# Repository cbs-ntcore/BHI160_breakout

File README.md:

# BHI160_breakout
Simple breakout board for the BHI160 IMU

WARNING this has not yet been ordered.

The project is available on oshpark https://oshpark.com/shared_projects/33BVj4D2

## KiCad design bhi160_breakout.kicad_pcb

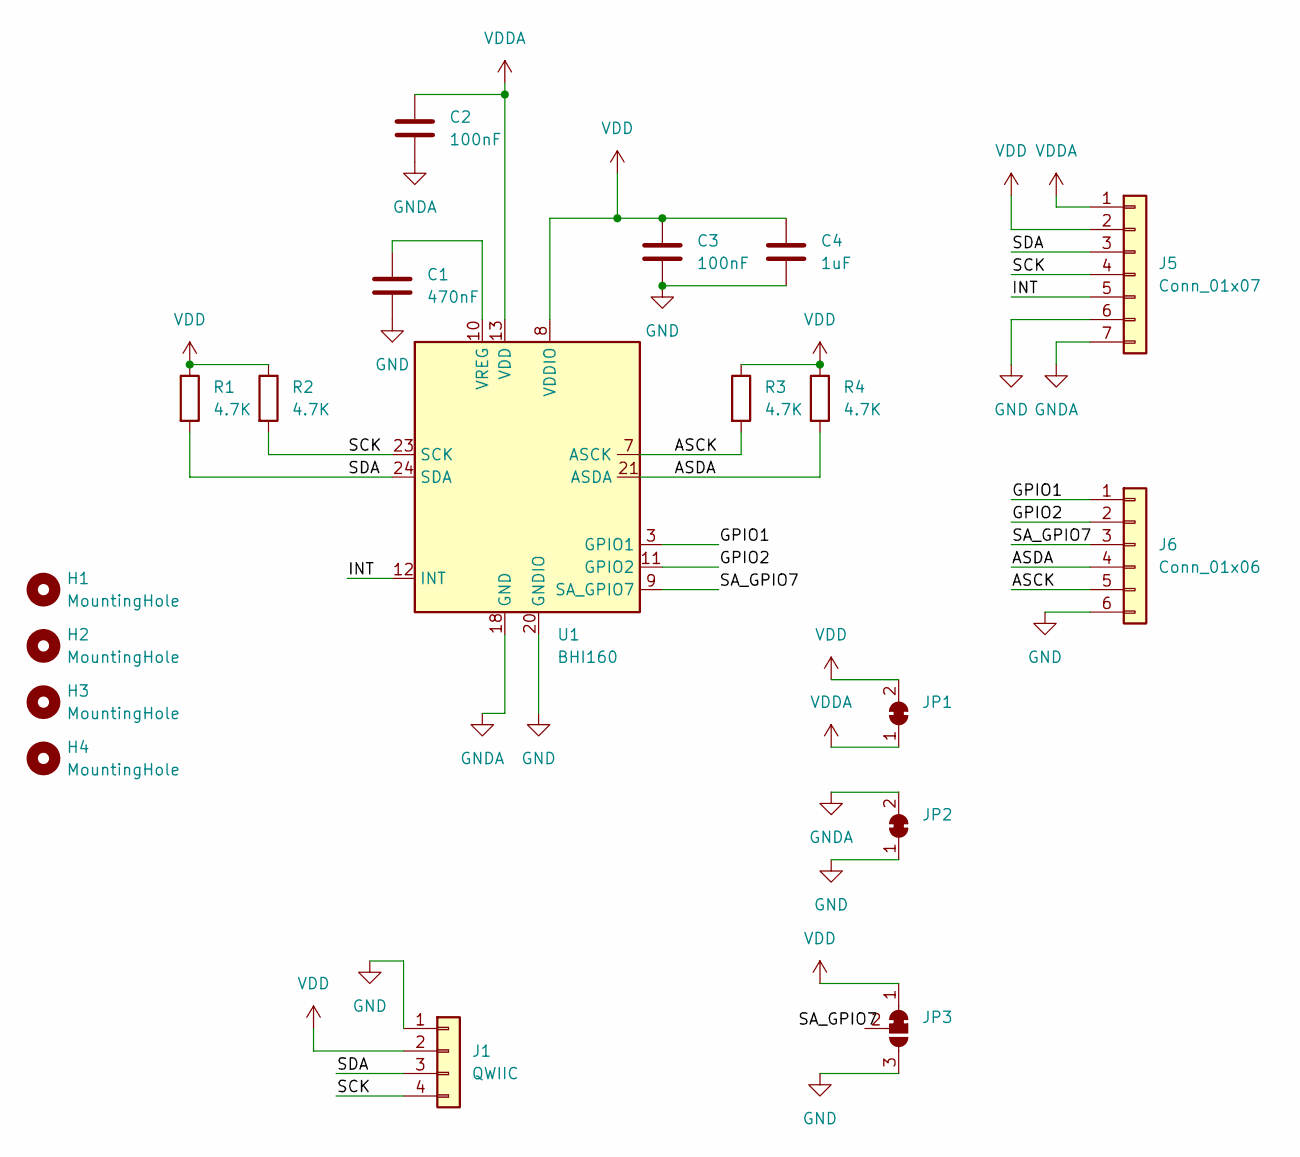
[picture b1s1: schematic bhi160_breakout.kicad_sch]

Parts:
C1: 470nF
C2, C3: 100nF
C4: 1uF
H1, H2, H3, H4: MountingHole; MountingHole_3.2mm_M3
J1: QWIIC; JST_SH_BM04B-SRSS-TB_1x04-1MP_P1.00mm_Vertical
J5: Conn_01x07; PinHeader_1x07_P2.54mm_Vertical
J6: Conn_01x06; PinHeader_1x06_P2.54mm_Vertical
JP1, JP2, JP3: (no value)
R1, R2, R3, R4: 4.7K
U1: BHI160; LGA-24_3x3mm_P0.4mm

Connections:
/ASCK: J6.5, R3.2, U1.7 (ASCK)
/ASDA: J6.4, R4.2, U1.21 (ASDA)
/GPIO1: J6.1, U1.3 (GPIO1)
/GPIO2: J6.2, U1.11 (GPIO2)
/INT: J5.5, U1.12 (INT)
/SA_GPIO7: J6.3, U1.9 (SA_GPIO7)
/SCK: J1.4, J5.4, R2.2, U1.23 (SCK)
/SDA: J1.3, J5.3, R1.2, U1.24 (SDA)
GND: C1.2, C3.2, C4.2, J1.1, J5.6, J6.6, JP2.1 (A), JP3.3 (B), U1.20 (GNDIO)
GNDA: C2.2, J5.7, JP2.2 (B), U1.18 (GND)
unnamed: C1.1, U1.10 (VREG)
VDD: C3.1, C4.1, J1.2, J5.2, JP1.2 (B), JP3.1 (A), R1.1, R2.1, R3.1, R4.1, U1.8 (VDDIO)
VDDA: C2.1, J5.1, JP1.1 (A), U1.13 (VDD)

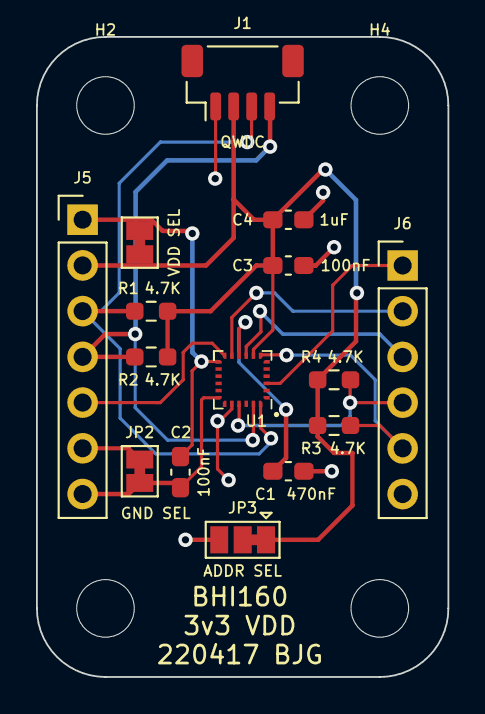
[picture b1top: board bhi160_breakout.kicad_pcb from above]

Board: 2 copper layers, 22.9 x 35.6 mm, 19 parts (0 on the bottom side), 13 nets.
